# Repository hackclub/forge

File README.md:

# Forge

Welcome to Forge! Forge is a [Hack Club](https://hackclub.com) YSWS program for teens to build hardware projects.

[Start forgin' it](https://forge.hackclub.com/?utm_source=github_readme)

## Contributing
Please see [the contributing tab](https://github.com/hackclub/forge?tab=contributing-ov-file#)

We're always looking for people to help with the platform! PRs are welcome. Local development and deployment instructions can be found [here](https://github.com/hackclub/forge/blob/main/development.md). PRs are welcome!

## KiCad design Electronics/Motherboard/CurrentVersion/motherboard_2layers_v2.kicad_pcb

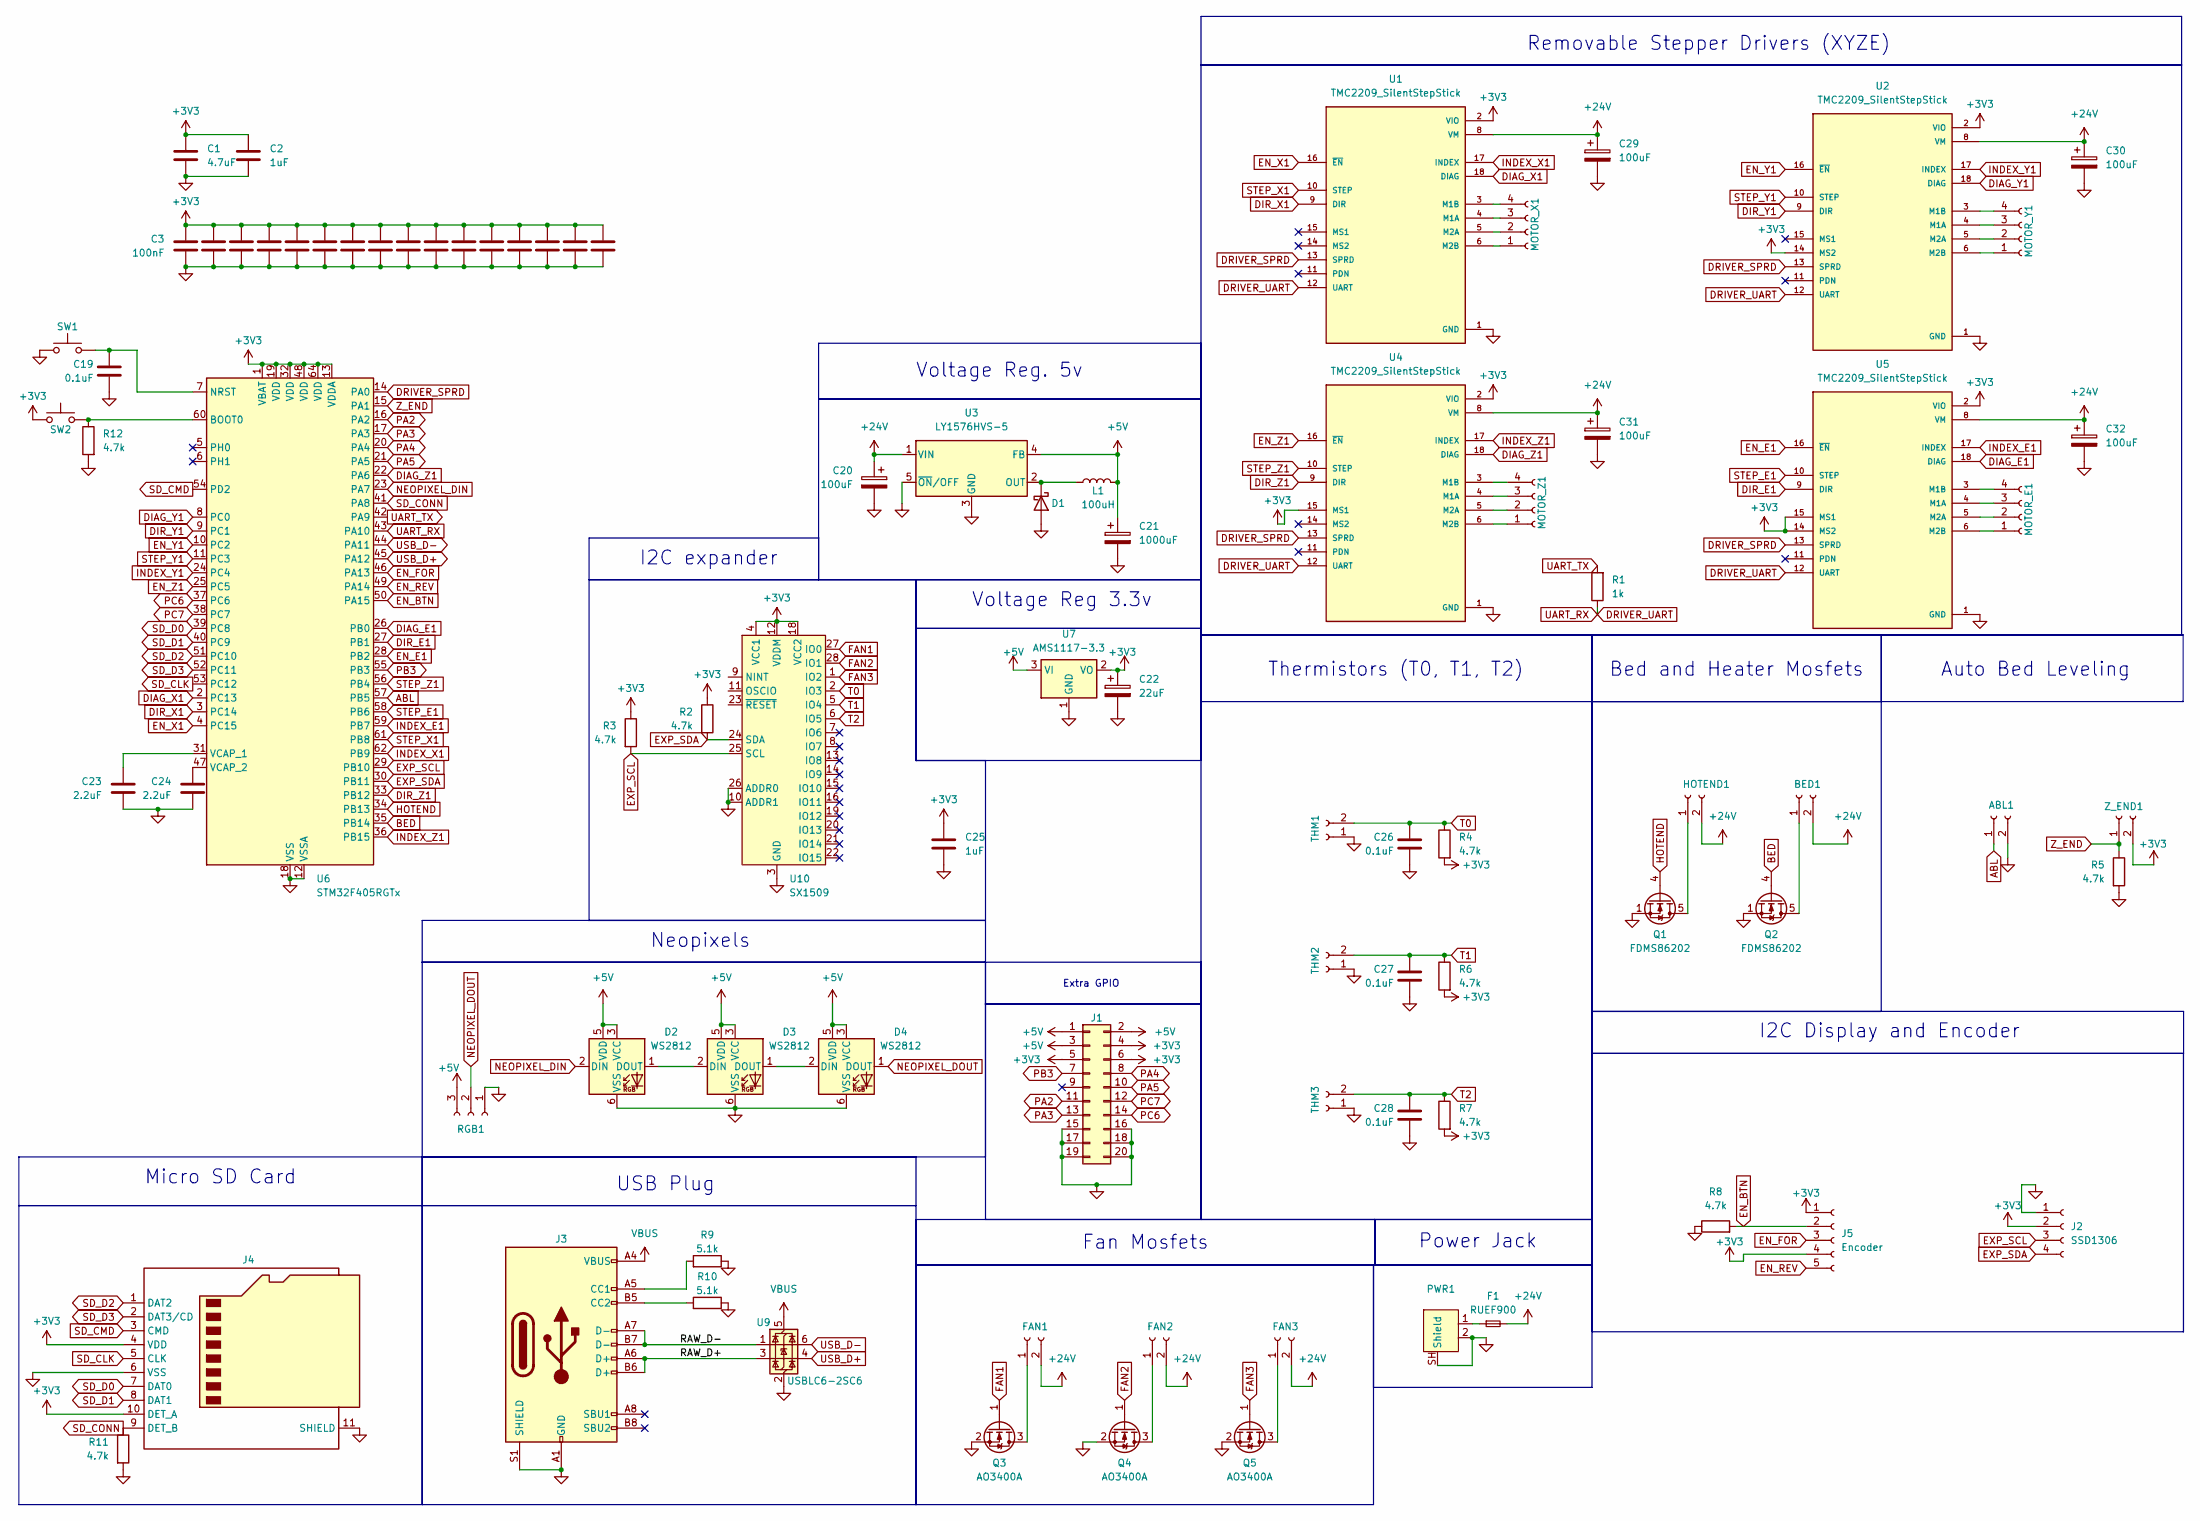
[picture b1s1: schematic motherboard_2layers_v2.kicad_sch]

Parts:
ABL1: Conn_01x02_Socket; JST_XH_B2B-XH-A_1x02_P2.50mm_Vertical
BED1: Conn_01x02_Socket; ScrewTerminal-2pin-MKDS_1_2-3_5
C1: 4.7uF; C_0603_1608Metric; Part # CGA0603X5R475K6R3JT
C2, C25: 1uF; C_0402_1005Metric; Part # TCC0402X5R105K6R3AT
C3, C4, C5, C6, C7, C8, C9, C10, C11, C12, C13, C14, C15, C16, C17, C18: 100nF; C_0201_0603Metric; Part # GRM033R61A104KE15D
C19, C26, C27, C28: 0.1uF; C_0402_1005Metric; Part # GCM155R71H104KE02J
C20: 100uF; CP_Elec_6.3x5.9; Part # EEE-FT1V101AP
C21: 1000uF; CP_EIA-7343-43_Kemet-X; Part # T491X108K006AT
C22: 22uF; CP_EIA-3216-18_Kemet-A; Part # CA45-A6R3K226T
C23, C24: 2.2uF; C_0603_1608Metric; Part # CC1206JKX7R8BB225
C29, C30, C31, C32: 100uF; CP_Elec_6.3x5.8; Part # EEEFT1V101AP
D1: D_Schottky; D_SOD-123; Part # C2972823
D2, D3, D4: WS2812; LED_WS2812_PLCC6_5.0x5.0mm_P1.6mm
F1: RUEF900; Fuse_RUEF900
FAN1, FAN2, FAN3: Conn_01x02_Socket; JST_XH_B2B-XH-A_1x02_P2.50mm_Vertical
HOTEND1: Conn_01x02_Socket; ScrewTerminal-2pin-MKDS_1_2-3_5
J1: Conn_02x10_Odd_Even; PinHeader_2x10_P2.54mm_Vertical
J2: SSD1306; JST_XH_B4B-XH-A_1x04_P2.50mm_Vertical
J3: USB_C_Receptacle_USB2.0_16P; USB_C_Receptacle_HRO_TYPE-C-31-M-12
J4: Micro_SD_Card_Det2; microSD_HC_Hirose_DM3AT-SF-PEJM5; LCSC Part # C114218
J5: Encoder; JST_XH_B5B-XH-A_1x05_P2.50mm_Vertical
L1: 100uH; L_0805_2012Metric; Part # WI0805LD101KST-C-HF
MOTOR_E1: Conn_01x04_Socket; JST_XH_B4B-XH-A_1x04_P2.50mm_Vertical
MOTOR_X1: Conn_01x04_Socket; JST_XH_B4B-XH-A_1x04_P2.50mm_Vertical
MOTOR_Y1: Conn_01x04_Socket; JST_XH_B4B-XH-A_1x04_P2.50mm_Vertical
MOTOR_Z1: Conn_01x04_Socket; JST_XH_B4B-XH-A_1x04_P2.50mm_Vertical
PWR1: XT30PW-M
Q1, Q2: FDMS86202; TDSON-8-1
Q3, Q4, Q5: AO3400A; SOT-23
R1: 1k; R_0603_1608Metric; Part # RC0603FR-131KL
R2, R3, R11, R12: 4.7k; R_0603_1608Metric; Part # RC1206JR-134K7L
R4, R5, R6, R7: 4.7k; R_1206_3216Metric; Part # RC1206JR-134K7L
R8: 4.7k; R_1206_3216Metric
R9, R10: 5.1k; R_0402_1005Metric; Part # RMCF0805JT5K10
RGB1: Conn_01x03_Socket; JST_XH_B3B-XH-A_1x03_P2.50mm_Vertical
SW1, SW2: ALPSALPINE_TopPush_Button; Part # SKHHAMA010
THM1, THM2, THM3: Conn_01x02_Socket; JST_XH_B2B-XH-A_1x02_P2.50mm_Vertical
U1, U2, U4, U5: TMC2209_SilentStepStick; MODULE_TMC2209_SILENTSTEPSTICK; PARTREV 1.20
U3: LY1576HVS-5; TO-263-5_TabPin3
U6: STM32F405RGTx; LQFP-64_10x10mm_P0.5mm
U7: AMS1117-3.3; SOT-223-3_TabPin2
U9: USBLC6-2SC6; SOT-23-6
U10: SX1509; QFN-28-1EP_4x4mm_P0.4mm_EP2.6x2.6mm
Z_END1: Conn_01x02_Socket; JST_XH_B2B-XH-A_1x02_P2.50mm_Vertical

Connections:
+3V3: C1.1, C2.1, C3.1, C4.1, C5.1, C6.1, C7.1, C8.1, C9.1, C10.1, C11.1, C12.1, C13.1, C14.1, C15.1, C16.1, C17.1, C18.1, C22.1, C25.1, J1.4, J1.5, J1.6, J2.2, J4.4 (VDD), J4.10 (DET_A), J5.1, J5.4, R2.1, R3.1, R4.2, R6.2, R7.2, SW2.1, U1.2 (VIO), U2.2 (VIO), U2.14 (MS2), U4.2 (VIO), U4.15 (MS1), U5.2 (VIO), U5.14 (MS2), U5.15 (MS1), U6.1 (VBAT), U6.13 (VDDA), U6.19 (VDD), U6.32 (VDD), U6.48 (VDD), U6.64 (VDD), U7.2 (VO), U10.4 (VCC1), U10.12 (VDDM), U10.18 (VCC2), Z_END1.2
+5V: C21.1, D2.3 (VCC), D2.5 (VDD), D3.3 (VCC), D3.5 (VDD), D4.3 (VCC), D4.5 (VDD), J1.1, J1.2, J1.3, L1.2, RGB1.3, U3.4 (FB), U7.3 (VI)
+24V: BED1.2, C20.1, C29.1, C30.1, C31.1, C32.1, F1.2, FAN1.2, FAN2.2, FAN3.2, HOTEND1.2, U1.8 (VM), U2.8 (VM), U3.1 (VIN), U4.8 (VM), U5.8 (VM)
/RAW_D+: J3.A6 (D+), J3.B6 (D+), U9.3 (I/O2)
/RAW_D-: J3.A7 (D-), J3.B7 (D-), U9.1 (I/O1)
ABL: ABL1.1, U6.57 (PB5)
BED: Q2.4 (G), U6.35 (PB14)
DIAG_E1: U5.18 (DIAG), U6.26 (PB0)
DIAG_X1: U1.18 (DIAG), U6.2 (PC13)
DIAG_Y1: U2.18 (DIAG), U6.8 (PC0)
DIAG_Z1: U4.18 (DIAG), U6.22 (PA6)
DIR_E1: U5.9 (DIR), U6.27 (PB1)
DIR_X1: U1.9 (DIR), U6.3 (PC14)
DIR_Y1: U2.9 (DIR), U6.9 (PC1)
DIR_Z1: U4.9 (DIR), U6.33 (PB12)
DRIVER_SPRD: U1.13 (SPRD), U2.13 (SPRD), U4.13 (SPRD), U5.13 (SPRD), U6.14 (PA0)
DRIVER_UART: R1.1, U1.12 (UART), U2.12 (UART), U4.12 (UART), U5.12 (UART), U6.43 (PA10)
EN_BTN: J5.2, R8.2, U6.50 (PA15)
EN_E1: U5.16 (~EN), U6.28 (PB2)
EN_FOR: J5.3, U6.46 (PA13)
EN_REV: J5.5, U6.49 (PA14)
EN_X1: U1.16 (~EN), U6.4 (PC15)
EN_Y1: U2.16 (~EN), U6.10 (PC2)
EN_Z1: U4.16 (~EN), U6.25 (PC5)
EXP_SCL: J2.3, R3.2, U6.29 (PB10), U10.25 (SCL)
EXP_SDA: J2.4, R2.2, U6.30 (PB11), U10.24 (SDA)
FAN1: Q3.1 (G), U10.27 (IO0)
FAN2: Q4.1 (G), U10.28 (IO1)
FAN3: Q5.1 (G), U10.1 (IO2)
GND: ABL1.2, C1.2, C2.2, C3.2, C4.2, C5.2, C6.2, C7.2, C8.2, C9.2, C10.2, C11.2, C12.2, C13.2, C14.2, C15.2, C16.2, C17.2, C18.2, C19.2, C20.2, C21.2, C22.2, C23.2, C24.2, C25.2, C26.2, C27.2, C28.2, C29.2, C30.2, C31.2, C32.2, D1.2 (A), D2.6 (VSS), D3.6 (VSS), D4.6 (VSS), J1.15, J1.16, J1.17, J1.18, J1.19, J1.20, J2.1, J3.A1 (GND), J3.A12 (GND), J3.B1 (GND), J3.B12 (GND), J3.S1 (SHIELD), J4.6 (VSS), J4.11 (SHIELD), PWR1.2, PWR1.SH (Shield), Q1.1 (S), Q1.2 (S), Q1.3 (S), Q2.1 (S), Q2.2 (S), Q2.3 (S), Q3.2 (S), Q4.2 (S), Q5.2 (S), R5.2, R8.1, R9.1, R10.1, R11.2, R12.2, RGB1.1, SW1.1, THM1.1, THM2.1, THM3.1, U1.1 (GND), U1.7 (GND), U2.1 (GND), U2.7 (GND), U3.3 (GND), U3.5 (~ON/OFF), U4.1 (GND), U4.7 (GND), U5.1 (GND), U5.7 (GND), U6.12 (VSSA), U6.18 (VSS), U6.63 (VSS), U7.1 (GND), U9.2 (GND), U10.3 (GND), U10.10 (ADDR1), U10.17 (GND), U10.26 (ADDR0)
HOTEND: Q1.4 (G), U6.34 (PB13)
INDEX_E1: U5.17 (INDEX), U6.59 (PB7)
INDEX_X1: U1.17 (INDEX), U6.62 (PB9)
INDEX_Y1: U2.17 (INDEX), U6.24 (PC4)
INDEX_Z1: U4.17 (INDEX), U6.36 (PB15)
NEOPIXEL_DIN: D2.2 (DIN), U6.23 (PA7)
NEOPIXEL_DOUT: D4.1 (DOUT), RGB1.2
unnamed: BED1.1, Q2.5 (D)
unnamed: D1.1 (K), L1.1, U3.2 (OUT)
unnamed: D2.1 (DOUT), D3.2 (DIN)
unnamed: D3.1 (DOUT), D4.2 (DIN)
unnamed: F1.1, PWR1.1
unnamed: FAN1.1, Q3.3 (D)
unnamed: FAN2.1, Q4.3 (D)
unnamed: FAN3.1, Q5.3 (D)
unnamed: HOTEND1.1, Q1.5 (D)
unnamed: J3.A5 (CC1), R9.2
unnamed: J3.B5 (CC2), R10.2
unnamed: MOTOR_E1.1, U5.6 (M2B)
unnamed: MOTOR_E1.2, U5.5 (M2A)
unnamed: MOTOR_E1.3, U5.4 (M1A)
unnamed: MOTOR_E1.4, U5.3 (M1B)
unnamed: MOTOR_X1.1, U1.6 (M2B)
unnamed: MOTOR_X1.2, U1.5 (M2A)
unnamed: MOTOR_X1.3, U1.4 (M1A)
unnamed: MOTOR_X1.4, U1.3 (M1B)
unnamed: MOTOR_Y1.1, U2.6 (M2B)
unnamed: MOTOR_Y1.2, U2.5 (M2A)
unnamed: MOTOR_Y1.3, U2.4 (M1A)
unnamed: MOTOR_Y1.4, U2.3 (M1B)
unnamed: MOTOR_Z1.1, U4.6 (M2B)
unnamed: MOTOR_Z1.2, U4.5 (M2A)
unnamed: MOTOR_Z1.3, U4.4 (M1A)
unnamed: MOTOR_Z1.4, U4.3 (M1B)
unnamed: R12.1, SW2.2, U6.60 (BOOT0)
unnamed: C19.1, SW1.2, U6.7 (NRST)
unnamed: C23.1, U6.31 (VCAP_1)
unnamed: C24.1, U6.47 (VCAP_2)
PA2: J1.11, U6.16 (PA2)
PA3: J1.13, U6.17 (PA3)
PA4: J1.8, U6.20 (PA4)
PA5: J1.10, U6.21 (PA5)
PB3: J1.7, U6.55 (PB3)
PC6: J1.14, U6.37 (PC6)
PC7: J1.12, U6.38 (PC7)
SD_CLK: J4.5 (CLK), U6.53 (PC12)
SD_CMD: J4.3 (CMD), U6.54 (PD2)
SD_CONN: J4.9 (DET_B), R11.1, U6.41 (PA8)
SD_D0: J4.7 (DAT0), U6.39 (PC8)
SD_D1: J4.8 (DAT1), U6.40 (PC9)
SD_D2: J4.1 (DAT2), U6.51 (PC10)
SD_D3: J4.2 (DAT3/CD), U6.52 (PC11)
STEP_E1: U5.10 (STEP), U6.58 (PB6)
STEP_X1: U1.10 (STEP), U6.61 (PB8)
STEP_Y1: U2.10 (STEP), U6.11 (PC3)
STEP_Z1: U4.10 (STEP), U6.56 (PB4)
T0: C26.1, R4.1, THM1.2, U10.2 (IO3)
T1: C27.1, R6.1, THM2.2, U10.5 (IO4)
T2: C28.1, R7.1, THM3.2, U10.6 (IO5)
UART_TX: R1.2, U6.42 (PA9)
USB_D+: U6.45 (PA12), U9.4 (I/O2)
USB_D-: U6.44 (PA11), U9.6 (I/O1)
VBUS: J3.A4 (VBUS), J3.A9 (VBUS), J3.B4 (VBUS), J3.B9 (VBUS), U9.5 (VBUS)
Z_END: R5.1, U6.15 (PA1), Z_END1.1

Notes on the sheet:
I2C Display and Encoder
Voltage Reg 3.3v
Auto Bed Leveling
I2C expander
Removable Stepper Drivers (XYZE)
Power Jack
USB Plug
Bed and Heater Mosfets
Extra GPIO
Neopixels
Fan Mosfets
Thermistors (T0, T1, T2)
Micro SD Card
Voltage Reg. 5v

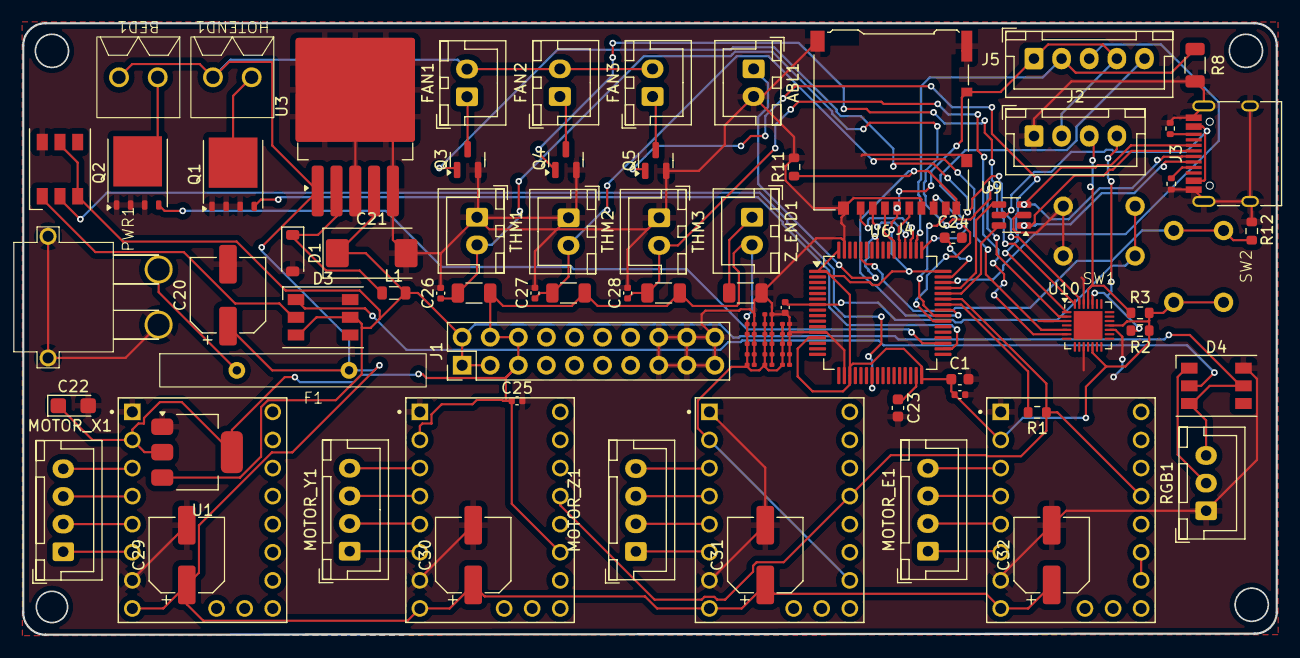
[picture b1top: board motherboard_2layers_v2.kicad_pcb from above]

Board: 2 copper layers, 113.4 x 55.3 mm, 87 parts (0 on the bottom side), 94 nets.

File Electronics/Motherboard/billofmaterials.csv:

"Id";"Designator";"Footprint";"Quantity";"Designation";"Supplier and ref";
1;"C32,C31,C29,C30";"CP_Elec_6.3x5.8";4;"100uF";;;
2;"C7,C14,C4,C9,C18,C15,C3,C16,C12,C6,C13,C17,C8,C10,C11,C5";"C_0201_0603Metric";16;"100nF";;;
3;"U7";"SOT-223-3_TabPin2";1;"AMS1117-3.3";;;
4;"R4,R8,R7,R6,R5";"R_1206_3216Metric";5;"4.7k";;;
5;"L1";"L_0805_2012Metric";1;"100uH";;;
6;"C27,C28,C19,C26";"C_0402_1005Metric";4;"0.1uF";;;
7;"R12,R2,R3,R11";"R_0603_1608Metric";4;"4.7k";;;
8;"J1";"PinHeader_2x10_P2.54mm_Vertical";1;"Conn_02x10_Odd_Even";;;
9;"D3,D4,D2";"LED_WS2812_PLCC6_5.0x5.0mm_P1.6mm";3;"WS2812";;;
10;"C24,C23";"C_0603_1608Metric";2;"2.2uF";;;
11;"J4";"microSD_HC_Hirose_DM3AT-SF-PEJM5";1;"Micro_SD_Card_Det2";;;
12;"Q5,Q3,Q4";"SOT-23";3;"AO3400A";;;
13;"Z_END1,FAN1,THM3,ABL1,FAN2,FAN3,THM1,THM2";"JST_XH_B2B-XH-A_1x02_P2.50mm_Vertical";8;"Conn_01x02_Socket";;;
14;"C20";"CP_Elec_6.3x5.9";1;"100uF";;;
15;"MOTOR_X1,MOTOR_Z1,MOTOR_E1,MOTOR_Y1";"JST_XH_B4B-XH-A_1x04_P2.50mm_Vertical";4;"Conn_01x04_Socket";;;
16;"U3";"TO-263-5_TabPin3";1;"LY1576HVS-5";;;
17;"U9";"SOT-23-6";1;"USBLC6-2SC6";;;
18;"C22";"CP_EIA-3216-18_Kemet-A";1;"22uF";;;
19;"C21";"CP_EIA-7343-43_Kemet-X";1;"1000uF";;;
20;"HOTEND1,BED1";"ScrewTerminal-2pin-MKDS_1_2-3_5";2;"Conn_01x02_Socket";;;
21;"Q1,Q2";"TDSON-8-1";2;"FDMS86202";;;
22;"R10,R9";"R_0402_1005Metric";2;"5.1k";;;
23;"U6";"LQFP-64_10x10mm_P0.5mm";1;"STM32F405RGTx";;;
24;"PWR1";"XT30PW-M";1;"~";;;
25;"D1";"D_SOD-123";1;"D_Schottky";;;
26;"J5";"JST_XH_B5B-XH-A_1x05_P2.50mm_Vertical";1;"Encoder";;;
27;"U10";"QFN-28-1EP_4x4mm_P0.4mm_EP2.6x2.6mm";1;"SX1509";;;
28;"R1";"R_0603_1608Metric";1;"1k";;;
29;"J3";"USB_C_Receptacle_HRO_TYPE-C-31-M-12";1;"USB_C_Receptacle_USB2.0_16P";;;
30;"SW1,SW2";"ALPSALPINE_TopPush_Button";2;"~";;;
31;"U1,U4,U5,U2";"MODULE_TMC2209_SILENTSTEPSTICK";4;"TMC2209_SilentStepStick";;;
32;"C25,C2";"C_0402_1005Metric";2;"1uF";;;
33;"RGB1";"JST_XH_B3B-XH-A_1x03_P2.50mm_Vertical";1;"Conn_01x03_Socket";;;
34;"J2";"JST_XH_B4B-XH-A_1x04_P2.50mm_Vertical";1;"SSD1306";;;
35;"C1";"C_0603_1608Metric";1;"4.7uF";;;

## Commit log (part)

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2026-06-13 new baseline for git diff
2026-06-14 expandable diff tree + journal order toggle in review
2026-06-14 expandable diff tree + journal order toggle in review (#326)
2026-06-14 add hours-in-pending-queue metric
2026-06-14 add hours pending metric (#327)
2026-06-14 add shop margin metric (coin value vs item cost)
2026-06-14 add shop margin metric (#328)
2026-06-14 prefill HCB card grant from order on fulfillment
2026-06-14 default orders admin to pending instead of my-orders
2026-06-14 orders: default to pending + prefilled HCB grant link (#329)
2026-06-14 fix AI check stalling on image-heavy READMEs
    The check ran FetchReadmeJob synchronously, which mirrored every README
    image to the CDN one at a time with no timeouts — minutes of work on
    image-heavy repos, redone on every run, so the check looked stuck. Now
    the check fetches README text only (mirror: false) and mirrors images in
    the background, with timeouts on all README/CDN calls and a cap on images
    mirrored per pass.
2026-06-14 fix AI check stalling on image heavy READMEs (#330)
2026-06-14 add admin impersonation (view as user)
    User-admins can view the app as a non-staff user from the admin user page.
    The real admin is parked in session[:impersonator_id]; while impersonating
    the session is strictly read-only — every non-GET request is blocked, so no
    orders/coins/submissions/edits can happen as the target. Start and stop are
    audited, a persistent banner shows who you're viewing as, and activity/streak/
    ahoy/onboarding side-effects are suppressed so it never touches their data.
2026-06-14 add impersonation (#331)
2026-06-14 let impersonators act for the user, block only coin spending
    The impersonation guard blocked all writes, so submitting a project (and its
    AI check) on a user's behalf got stuck/blocked. Now only ShopController#create
    (the sole user-facing coin-spending path) is blocked while impersonating —
    submissions, edits, and devlogs go through. Admin money actions stay
    unreachable since the impersonated user isn't staff.
2026-06-14 improve impersonating
2026-06-14 auto-restart stale AI checks instead of showing 'stalled' forever
    A check whose worker died/hung leaves ai_check_result stuck at running in the
    DB; the display flips it to 'stalled — run it again' but nothing ever re-runs
    it, so projects like 464 look permanently stuck. Now visiting the check page
    detects a stale result and kicks a fresh run server-side (works even while
    impersonating, since it's a GET), so it self-heals.
2026-06-14 drop birthday from ai-check test (CodeQL); use XHR to skip reauth
2026-06-14 auto-restart stale AI checks (#333)
2026-06-14 make AI check page recover from an errored result
    An errored/stalled ai_check_result rendered nothing — no spinner, no message,
    no retry, no submit — so the page looked frozen (e.g. project 464). Now an
    error shows an actionable card on load with Re-run, Submit-anyway, and Back, so
    a failed check is never a dead-end.
2026-06-14 make AI check page recover from an errored result, drop added comments
    An errored or stalled ai_check_result rendered nothing, so the page looked
    frozen. It now shows a card with re-run, submit-anyway, and back. Also removes
    the explanatory comments added across the recent AI-check and impersonation work.
2026-06-14 fix AI checker AGAIN (#334)
2026-06-14 add HCB budget metric to admin metrics page
2026-06-14 add HCB budget metric to admin metrics page (#335)
2026-06-14 add made-with-AI declaration and badge to projects
2026-06-14 made with AI badge
2026-06-14 show made-with-AI badge on the review screen
2026-06-14 show made-with-AI badge on the review screen (#337)
2026-06-14 show guild invites instead of member count in guild lists
2026-06-14 show guild invites instead of member count in guild lists (#338)
2026-06-15 add admin button to convert a project between design and build review
2026-06-15 add admin button to convert a project between design and build review (#339)
2026-06-15 let builders submit while the pre-submission check is still running
2026-06-15 set @project for convert_review_type so the action doesn't crash
2026-06-15 fix ai checker AGAIN
2026-06-15 add hours-per-person, approved hours, coin rate graph, and 20k hours goal to admin metrics
2026-06-15 add a buncha metrics
2026-06-16 Bump vite from 8.0.10 to 8.0.16
    Bumps [vite](https://github.com/vitejs/vite/tree/HEAD/packages/vite) from 8.0.10 to 8.0.16.
    - [Release notes](https://github.com/vitejs/vite/releases)
    - [Changelog](https://github.com/vitejs/vite/blob/main/packages/vite/CHANGELOG.md)
    - [Commits](https://github.com/vitejs/vite/commits/v8.0.16/packages/vite)
    ---
    updated-dependencies:
2026-06-17 change AI model
2026-06-18 change AI model (#343)
2026-06-19 Bump actions/checkout from 6 to 7
    Bumps [actions/checkout](https://github.com/actions/checkout) from 6 to 7.
    - [Release notes](https://github.com/actions/checkout/releases)
    - [Changelog](https://github.com/actions/checkout/blob/main/CHANGELOG.md)
    - [Commits](https://github.com/actions/checkout/compare/v6...v7)
    ---
    updated-dependencies:
2026-06-20 keep devlogs visible when a draft project is converted to tier 1
2026-06-20 keep devlogs visible when a draft project is converted to tier 1 (#345)
2026-06-22 Bump form-data from 4.0.5 to 4.0.6
    Bumps [form-data](https://github.com/form-data/form-data) from 4.0.5 to 4.0.6.
    - [Changelog](https://github.com/form-data/form-data/blob/master/CHANGELOG.md)
    - [Commits](https://github.com/form-data/form-data/compare/v4.0.5...v4.0.6)
    ---
    updated-dependencies:
    - dependency-name: form-data
2026-06-22 surface failing and stalled AI checks
2026-06-22 surface failing AI checks (#347)
2026-06-22 surface failing AI checks (#347) (#348)
2026-06-22 Fixed the built filter in the explore page
2026-06-22 fixed bug in controllers
2026-06-23 Bump nokogiri from 1.19.3 to 1.19.4
    Bumps [nokogiri](https://github.com/sparklemotion/nokogiri) from 1.19.3 to 1.19.4.
    - [Release notes](https://github.com/sparklemotion/nokogiri/releases)
    - [Changelog](https://github.com/sparklemotion/nokogiri/blob/main/CHANGELOG.md)
    - [Commits](https://github.com/sparklemotion/nokogiri/compare/v1.19.3...v1.19.4)
    ---
    updated-dependencies:
2026-06-23 Bump faraday from 2.14.1 to 2.14.3
    Bumps [faraday](https://github.com/lostisland/faraday) from 2.14.1 to 2.14.3.
    - [Release notes](https://github.com/lostisland/faraday/releases)
    - [Changelog](https://github.com/lostisland/faraday/blob/main/CHANGELOG.md)
    - [Commits](https://github.com/lostisland/faraday/compare/v2.14.1...v2.14.3)
    ---
    updated-dependencies:
2026-06-24 Bump concurrent-ruby from 1.3.6 to 1.3.7
    Bumps [concurrent-ruby](https://github.com/ruby-concurrency/concurrent-ruby) from 1.3.6 to 1.3.7.
    - [Release notes](https://github.com/ruby-concurrency/concurrent-ruby/releases)
    - [Changelog](https://github.com/ruby-concurrency/concurrent-ruby/blob/master/CHANGELOG.md)
    - [Commits](https://github.com/ruby-concurrency/concurrent-ruby/compare/v1.3.6...v1.3.7)
    ---
    updated-dependencies:
2026-06-25 FIX AI
2026-06-25 fix ai AGAIN (#353)
    * change AI model
    * surface failing AI checks (#347)
    * FIX AI
2026-06-27 Modify coin rates for project tiers
    Updated coin rates for project tiers.
2026-06-27 Modify coin rates for project tiers (#354)
    Updated coin rates for project tiers.
2026-06-28 fix group projects
2026-06-28 fix group projects (#355)
